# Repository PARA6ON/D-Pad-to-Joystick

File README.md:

# D-Pad-to-Joystick
Module to go from a D-pad to a Joystick

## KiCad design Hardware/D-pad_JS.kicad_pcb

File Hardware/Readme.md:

Hardware description will be here:

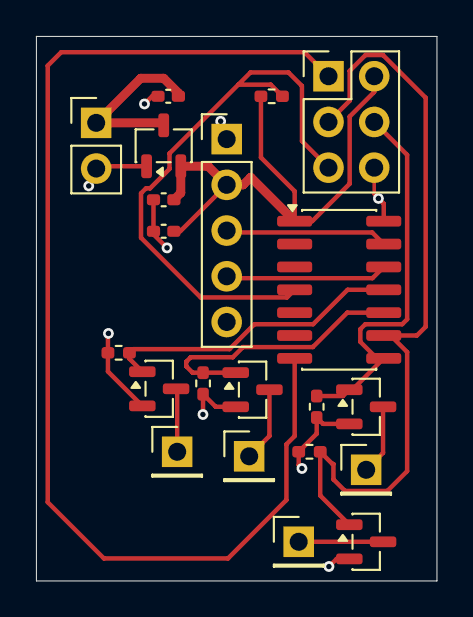
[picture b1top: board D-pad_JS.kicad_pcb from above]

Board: 2 copper layers, 22.2 x 30.2 mm, 21 parts (0 on the bottom side), 15 nets.

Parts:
C1, C2: 1uF; C_0402_1005Metric_Pad0.74x0.62mm_HandSolder
C3: 100nF; C_0402_1005Metric_Pad0.74x0.62mm_HandSolder
J1: Joystick; PinHeader_1x05_P2.54mm_Vertical
J2: Battery; PinHeader_1x02_P2.54mm_Vertical
J3: ICSP; PinHeader_2x03_P2.54mm_Vertical
J_DOWN_TRACE1: Conn_01x01_Socket; PinHeader_1x01_P2.54mm_Vertical
J_LEFT_TRACE1: Conn_01x01_Socket; PinHeader_1x01_P2.54mm_Vertical
J_RIGHT_TRACE1: Conn_01x01_Socket; PinHeader_1x01_P2.54mm_Vertical
J_UP_TRACE1: Conn_01x01_Socket; PinHeader_1x01_P2.54mm_Vertical
Q5, Q6, Q7, Q8: 2N7002; SOT-23
R1, R5, R6, R7, R8: 10k; R_0402_1005Metric_Pad0.72x0.64mm_HandSolder
U1: XC6206P332MR; SOT-23-3
U2: ATtiny84-20SS; SOIC-14_3.9x8.7mm_P1.27mm

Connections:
/Vcc: C1.1, J2.1, U1.3 (VI)
/transistors/DOWN: Q6.1 (G), R6.2, U2.10 (PA3)
/transistors/LEFT: J3.3, Q7.1 (G), R7.1, U2.9 (PA4)
/transistors/RIGHT: J3.4, Q8.1 (G), R8.1, U2.8 (PA5)
/transistors/UP: Q5.1 (G), R5.2, U2.11 (PA2)
GND: C1.2, C2.1, C3.1, J1.1, J2.2, J3.6, Q5.2 (S), Q6.2 (S), Q7.2 (S), Q8.2 (S), R5.1, R6.1, R7.2, R8.2, U1.1 (GND), U2.14 (GND)
unnamed: C2.2, C3.2, J1.2, J3.2, R1.2, U1.2 (VO), U2.1 (VCC)
unnamed: J1.3, U2.13 (AREF/PA0)
unnamed: J1.4, U2.12 (PA1)
unnamed: J3.1, U2.7 (PA6)
unnamed: J3.5, R1.1, U2.4 (~RESET/PB3)
unnamed: J_DOWN_TRACE1.1, Q6.3 (D)
unnamed: J_LEFT_TRACE1.1, Q7.3 (D)
unnamed: J_RIGHT_TRACE1.1, Q8.3 (D)
unnamed: J_UP_TRACE1.1, Q5.3 (D)
